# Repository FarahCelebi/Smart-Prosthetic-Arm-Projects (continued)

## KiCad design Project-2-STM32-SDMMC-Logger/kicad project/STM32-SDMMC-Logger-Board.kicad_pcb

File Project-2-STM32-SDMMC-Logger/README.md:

# STM32-SDMMC-Logger

An STM32F411-based data logger board with a 4-bit SDMMC interface to a
microSD card slot, designed as a companion to the EMG Acquisition Board.
The board receives dual-channel EMG data over I²C and logs it to a microSD
card in real time via FatFS, providing a self-contained data capture platform
for training the gesture classification firmware in the Smart Prosthetic Arm
system.

## Schematic

## PCB Layout

## 3D View

## Overview

The board pairs an STM32F411RETx (LQFP-64) with a push-push microSD card
slot over the SDMMC peripheral's 4-bit wide bus, capable of sustained write
speeds suitable for real-time dual-channel EMG logging at 1kHz sample rate.
A 25MHz crystal provides the accurate clock reference required for USB CDC
operation. Power comes from a micro-USB connector through a polyfuse and
AMS1117-3.3 LDO. A 4-pin I²C header matches the pinout of the EMG
Acquisition Board's J3 connector for direct cable connection.

## Design Notes

**MCU package selection:** The STM32F411 is available in UFQFPN-48 and
LQFP-64 packages. The UFQFPN-48 was initially considered but rejected because
the SDMMC peripheral requires PC8–PC12 and PD2, which are not bonded out on
the 48-pin package. The LQFP-64 exposes the full port C and port D, making
it the only viable option for 4-bit SDMMC operation on this device.

**SDMMC bus:** CLK, CMD, and DAT0–DAT3 connect the STM32's SDMMC peripheral
to the card slot using the standard STM32F4 pin mapping (PC12, PD2,
PC8–PC11). Each signal passes through a 47Ω series resistor placed close to
the STM32 to damp reflections at the card connector end. CMD and DAT0–DAT3
each have a 10kΩ pull-up to +3.3V — required by the SD specification to hold
these lines high during card initialisation before the card begins responding.
CLK has no pull-up since it is a push-pull output driven continuously by the
peripheral and is never in a high-impedance state.

**SDMMC signal integrity:** All six SDMMC signals are routed at 0.25mm width
on F.Cu with lengths kept as short as possible given the placement. The series
resistors are placed inline on each trace close to U2's pins. At the initial
operating frequency of 25MHz (half-speed mode, as used by FatFS during card
initialisation and typical logging workloads), the timing budget is generous
and the short trace lengths keep skew well within tolerance.

**Card detect:** The microSD connector includes a mechanical DET switch that
closes to GND when a card is inserted. This connects to PB7 with a 10kΩ
pull-up to +3.3V, keeping the GPIO high when no card is present and pulling
it low on insertion. The DAT3/CD pin on the card is used exclusively as DAT3
during normal 4-bit operation — the mechanical DET switch is used for card
presence detection to avoid conflicts with the data bus.

**Crystal and USB:** A 25MHz crystal (KC2520Z, 4-pad SMD) provides the
external clock reference for the STM32's PLL and USB peripheral. Load
capacitors C13 and C14 (12pF each) are placed immediately beside the PH0
and PH1 pins on U2, with no vias on the oscillator traces. The calculated
load capacitance is approximately 9pF, consistent with the crystal's
specification. USB D+ and D− are routed as a matched pair through the
USBLC6-2SC6 ESD protection device placed close to J1, then through 22Ω
series resistors before reaching PA11 and PA12.

**Power supply:** VBUS from J1 passes through a 500mA polyfuse (F1) before
reaching the AMS1117-3.3 LDO (U1). The polyfuse protects the USB host from
overcurrent faults and resets automatically once the fault clears. The LDO
input is decoupled with 10µF and 100nF capacitors; the output is decoupled
with 10µF and 100nF capacitors. All downstream logic and analog circuitry
runs from the 3.3V output.

**Stackup rationale:** This board uses a 2-layer stackup with signals and
power on F.Cu and a solid unbroken GND plane on B.Cu only — no GND pour on
F.Cu. For a digital board this configuration gives every F.Cu signal trace a
direct return path immediately beneath it, which is the optimal arrangement
for signal integrity. Adding a GND pour on F.Cu would fragment it with signal
traces, creating isolated copper islands that require stitching vias and
producing inconsistent return paths under SDMMC and USB signals. The solid
B.Cu plane handles all return currents cleanly without these compromises.
Stitching vias are placed around the board perimeter to tie the board edge
GND connections to the B.Cu plane.

**Decoupling:** The STM32F411RETx has four VDD pins and one VDDA pin, each
decoupled individually with a 100nF ceramic capacitor placed as close as
physically possible to the respective pin. The single VCAP1 pin is decoupled
with a 1µF capacitor as required by the internal core voltage regulator.
VBAT is decoupled with 100nF to GND.

## Manufacturing

- 2-layer stackup: F.Cu (signal + power) / B.Cu (solid GND plane)
- 1.6mm FR4, standard 1oz copper
- Passed DRC with 0 violations, 0 unconnected nets
- Gerbers and drill files generated

## Part of

Smart Prosthetic Arm — STM32-SDMMC-Logger #2

## Tools

- KiCad

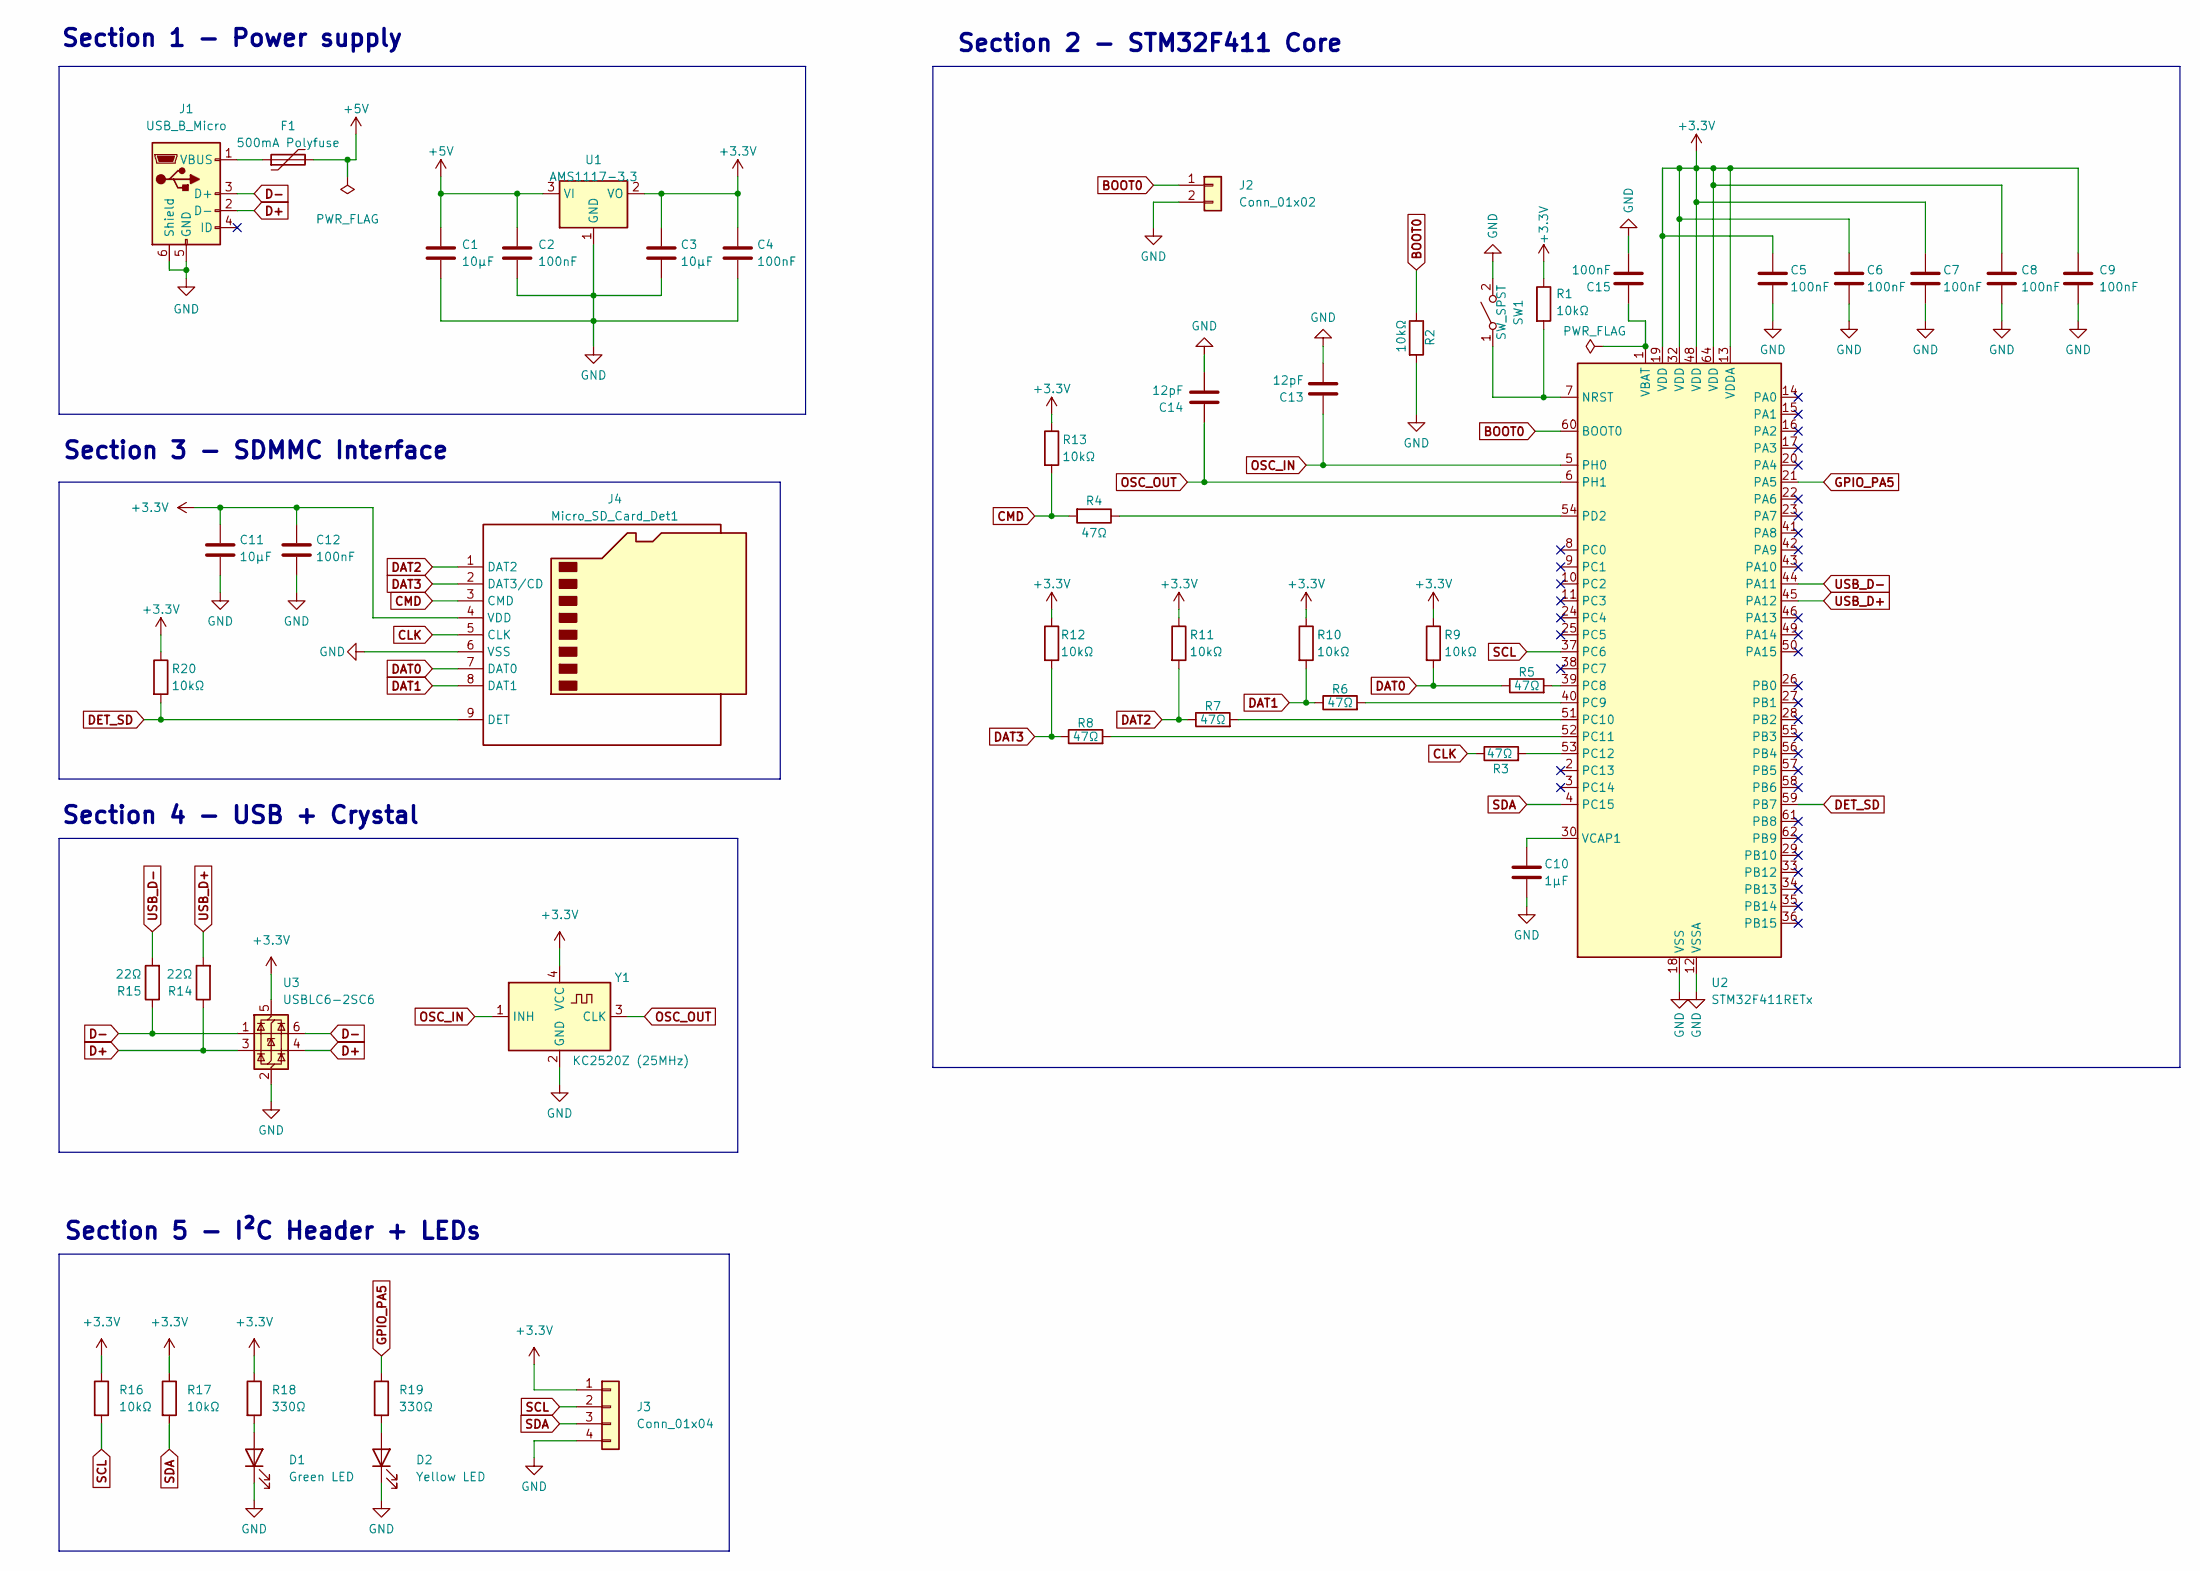
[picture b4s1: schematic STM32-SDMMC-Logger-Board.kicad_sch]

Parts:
C1, C3, C11: 10µF; C_0805_2012Metric
C2, C4, C5, C6, C7, C8, C9, C12, C15: 100nF; C_0402_1005Metric
C10: 1µF; C_0402_1005Metric
C13, C14: 12pF; C_0402_1005Metric
D1: Green LED; LED_0402_1005Metric
D2: Yellow LED; LED_0402_1005Metric
F1: 500mA Polyfuse; Fuse_1812_4532Metric
J1: USB_B_Micro; USB_Micro-B_Amphenol_10118194_Horizontal
J2: Conn_01x02; PinHeader_1x02_P2.54mm_Vertical
J3: Conn_01x04; FanPinHeader_1x04_P2.54mm_Vertical
J4: Micro_SD_Card_Det1; microSD_HC_Molex_47219-2001
R1, R2, R9, R10, R11, R12, R13, R16, R17, R20: 10kΩ; R_0402_1005Metric
R3, R4, R5, R6, R7, R8: 47Ω; R_0402_1005Metric
R14, R15: 22Ω; R_0402_1005Metric
R18, R19: 330Ω; R_0402_1005Metric
SW1: SW_SPST; SW_SPST_PTS645Sx43SMTR92
U1: AMS1117-3.3; SOT-223-3_TabPin2
U2: STM32F411RETx; LQFP-64_10x10mm_P0.5mm
U3: USBLC6-2SC6; SOT-23-6
Y1: KC2520Z (25MHz); Crystal_SMD_2520-4Pin_2.5x2.0mm

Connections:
+3.3V: C3.1, C4.1, C5.1, C6.1, C7.1, C8.1, C9.1, C11.1, C12.1, J3.1, J4.4 (VDD), R1.1, R9.1, R10.1, R11.1, R12.1, R13.1, R16.1, R17.1, R18.1, R20.1, U1.2 (VO), U2.13 (VDDA), U2.19 (VDD), U2.32 (VDD), U2.48 (VDD), U2.64 (VDD), U3.5 (VBUS), Y1.4 (VCC)
+5V: C1.1, C2.1, F1.2, U1.3 (VI)
BOOT0: J2.1, R2.1, U2.60 (BOOT0)
CLK: J4.5 (CLK), R3.1
CMD: J4.3 (CMD), R4.2, R13.2
D+: J1.2 (D-), R14.1, U3.3 (I/O2), U3.4 (I/O2)
D-: J1.3 (D+), R15.1, U3.1 (I/O1), U3.6 (I/O1)
DAT0: J4.7 (DAT0), R5.1, R9.2
DAT1: J4.8 (DAT1), R6.1, R10.2
DAT2: J4.1 (DAT2), R7.1, R11.2
DAT3: J4.2 (DAT3/CD), R8.1, R12.2
DET_SD: J4.9 (DET), R20.2, U2.59 (PB7)
GND: C1.2, C2.2, C3.2, C4.2, C5.2, C6.2, C7.2, C8.2, C9.2, C10.2, C11.2, C12.2, C13.2, C14.2, C15.2, D1.1 (K), D2.1 (K), J1.5 (GND), J1.6 (Shield), J2.2, J3.4, J4.6 (VSS), R2.2, SW1.2 (B), U1.1 (GND), U2.12 (VSSA), U2.18 (VSS), U2.31 (VSS), U2.47 (VSS), U2.63 (VSS), U3.2 (GND), Y1.2 (GND)
GPIO_PA5: R19.1, U2.21 (PA5)
unnamed: D1.2 (A), R18.2
unnamed: D2.2 (A), R19.2
unnamed: F1.1, J1.1 (VBUS)
unnamed: R1.2, SW1.1 (A), U2.7 (NRST)
unnamed: R5.2, U2.39 (PC8)
unnamed: R6.2, U2.40 (PC9)
unnamed: R7.2, U2.51 (PC10)
unnamed: R8.2, U2.52 (PC11)
unnamed: R3.2, U2.53 (PC12)
unnamed: R4.1, U2.54 (PD2)
unnamed: C15.1, U2.1 (VBAT)
unnamed: C10.1, U2.30 (VCAP1)
OSC_IN: C13.1, U2.5 (PH0), Y1.1 (INH)
OSC_OUT: C14.1, U2.6 (PH1), Y1.3 (CLK)
SCL: J3.2, R16.2, U2.37 (PC6)
SDA: J3.3, R17.2, U2.4 (PC15)
USB_D+: R14.2, U2.45 (PA12)
USB_D-: R15.2, U2.44 (PA11)

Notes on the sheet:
Section 3 - SDMMC Interface
Section 2 - STM32F411 Core
Section 4 - USB + Crystal
Section 1 - Power supply
Section 5 - I²C Header + LEDs

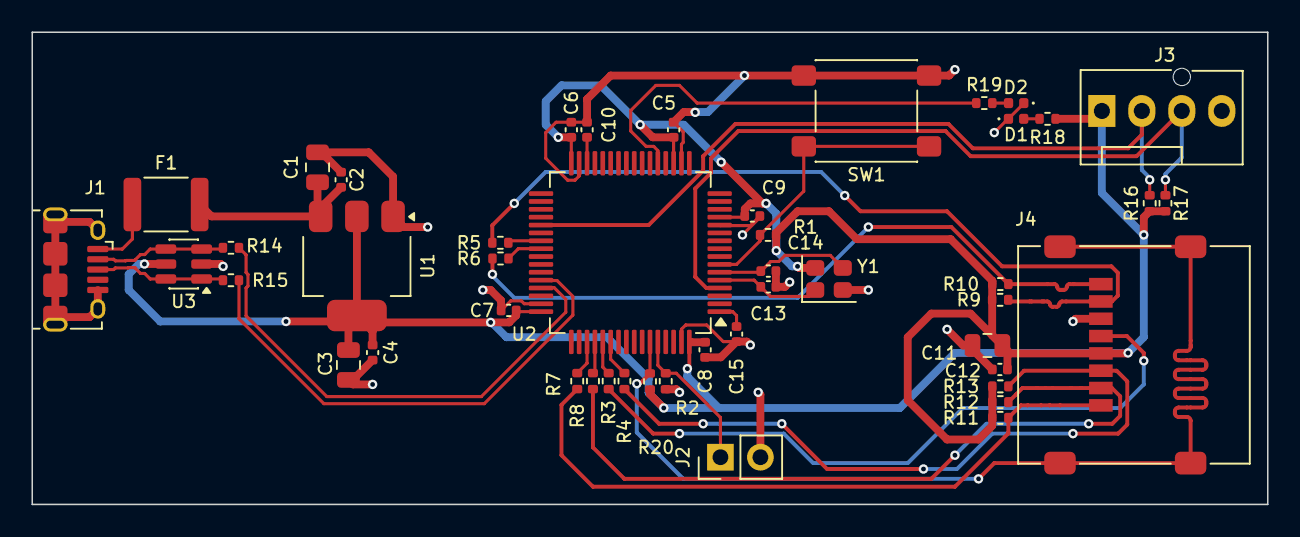
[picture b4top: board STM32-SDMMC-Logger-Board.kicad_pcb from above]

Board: 2 copper layers, 78.5 x 30.0 mm, 47 parts (0 on the bottom side), 32 nets.

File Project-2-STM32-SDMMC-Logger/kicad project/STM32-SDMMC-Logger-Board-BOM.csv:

"Id";"Designator";"Footprint";"Quantity";"Designation";"Supplier and ref";
1;"C14,C13";"C_0402_1005Metric";2;"12pF";;;
2;"Y1";"Crystal_SMD_2520-4Pin_2.5x2.0mm";1;"KC2520Z (25MHz)";;;
3;"R14,R15";"R_0402_1005Metric";2;"22Ω";;;
4;"U3";"SOT-23-6";1;"USBLC6-2SC6";;;
5;"F1";"Fuse_1812_4532Metric";1;"500mA Polyfuse";;;
6;"R10,R9,R1,R20,R12,R16,R17,R11,R2,R13";"R_0402_1005Metric";10;"10kΩ";;;
7;"C1,C11,C3";"C_0805_2012Metric";3;"10µF";;;
8;"C10";"C_0402_1005Metric";1;"1µF";;;
9;"J2";"PinHeader_1x02_P2.54mm_Vertical";1;"Conn_01x02";;;
10;"R19,R18";"R_0402_1005Metric";2;"330Ω";;;
11;"C8,C2,C7,C12,C6,C4,C9,C15,C5";"C_0402_1005Metric";9;"100nF";;;
12;"D1";"LED_0402_1005Metric";1;"Green LED";;;
13;"SW1";"SW_SPST_PTS645Sx43SMTR92";1;"SW_SPST";;;
14;"U1";"SOT-223-3_TabPin2";1;"AMS1117-3.3";;;
15;"J3";"FanPinHeader_1x04_P2.54mm_Vertical";1;"Conn_01x04";;;
16;"R3,R6,R4,R5,R8,R7";"R_0402_1005Metric";6;"47Ω";;;
17;"J1";"USB_Micro-B_Amphenol_10118194_Horizontal";1;"USB_B_Micro";;;
18;"D2";"LED_0402_1005Metric";1;"Yellow LED";;;
19;"U2";"LQFP-64_10x10mm_P0.5mm";1;"STM32F411RETx";;;
20;"J4";"microSD_HC_Molex_47219-2001";1;"Micro_SD_Card_Det1";;;

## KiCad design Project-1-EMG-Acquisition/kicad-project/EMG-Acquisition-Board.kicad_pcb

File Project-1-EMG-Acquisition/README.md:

# EMG-Acquisition-Board

A dual-channel electromyography (EMG) signal acquisition board for surface
electrode input, designed as Project 1 of the Smart Prosthetic Arm system.
The board conditions raw muscle electrical signals into a clean, amplified,
digitised output suitable for real-time gesture classification firmware.

## Schematic

## PCB Layout

## 3D View

## Overview

Surface EMG signals are weak (50µV–5mV), heavily contaminated by DC electrode
offset, motion artefact, and 50Hz mains interference. This board addresses
each of these with a structured four-stage signal chain: differential
instrumentation amplification, AC coupling, a second gain stage, and
anti-alias filtering before a 16-bit I²C ADC. Total gain per channel is
approximately 404×, placing a 1mV EMG input at roughly 400mV at the ADC input
— well within the ADS1115's input range referenced to a 1.65V mid-rail.

## Design Notes

**Mid-rail bias generation:** The entire analog chain operates from a single
3.3V supply, which requires a stable 1.65V mid-rail reference to centre
signals within the supply range. A resistor divider (R1, R2 — 100kΩ each)
sets the VMID node at 1.65V, filtered by a 10µF capacitor (C3) to suppress
supply noise. A TLV6001DCK op-amp wired as a unity-gain voltage follower
buffers this reference (VMID_BUF), providing a low-impedance 1.65V rail that
drives the INA333 REF pins and the second-stage amplifier bias inputs. Without
the buffer, loading from the REF pins would pull VMID off its setpoint under
signal conditions.

**First-stage instrumentation amplifier:** Each channel uses an INA333 (SOIC-8)
configured for approximately 101× differential gain, set by a single 1kΩ gain
resistor (Rg) via the formula G = 1 + 100kΩ/Rg. The INA333 was selected for
its low offset voltage (25µV typical), low input bias current suitable for
high-impedance electrode sources, and single-supply rail-to-rail operation
down to 1.8V. The REF pin is tied to VMID_BUF on both channels, centering
the amplifier output at 1.65V. Input bias resistors (R3, R4 and R6, R7 —
1MΩ each) hold each differential input at VMID_BUF when no electrode is
connected, preventing the instrumentation amplifier inputs from floating and
the output from railing.

**AC coupling and high-pass filter:** The INA333 output passes through an RC
high-pass filter (C5/C7 — 10µF, R5/R8 — 10kΩ) with a cutoff frequency of
approximately 1.6Hz, calculated as f = 1/(2π × 10kΩ × 10µF). This removes
the residual DC electrode offset that survives the differential stage —
typically several hundred millivolts in practical electrode setups — while
passing all physiologically relevant EMG content above 20Hz with minimal
attenuation.

**Second-stage amplifier:** A TLV2372 dual op-amp (SOIC-8) provides 4×
additional gain per channel in a non-inverting topology, with the output
biased at VMID_BUF through the lower feedback resistor. Gain is set by the
ratio 1 + R13/R11 = 1 + 30kΩ/10kΩ = 4×. This stage also drives the
anti-alias filter, which a high-output-impedance source such as the RC filter
output could not do reliably.

**Anti-alias filter:** A first-order RC low-pass filter (R15/R16 — 3.3kΩ,
C9/C10 — 100nF) on each channel output sets the anti-alias cutoff at
approximately 480Hz, calculated as f = 1/(2π × 3.3kΩ × 100nF). This sits
just below the Nyquist frequency for a 1kHz ADC sampling rate, suppressing
out-of-band noise and aliasing artefacts before the signal reaches the ADC
input.

**ADC and I²C interface:** The ADS1115IDGS (MSOP-10) is a 16-bit successive-
approximation ADC with an internal programmable gain amplifier and I²C
interface. Channels AIN0 and AIN1 receive CH1_ADC and CH2_ADC respectively;
AIN2 and AIN3 are tied to GND. The ADDR pin is tied to GND, setting the I²C
address to 0x48. VDD is decoupled with a 100nF ceramic capacitor and a 10µF
bulk capacitor. I²C pull-up resistors (R17, R18 — 10kΩ each to +3.3V) are
placed immediately adjacent to J3, the 4-pin I²C header (VCC, GND, SCL, SDA),
which connects to the host microcontroller.

**Signal chain summary:**

| Stage | Component | Gain / Function |
|---|---|---|
| Instrumentation amp | INA333 × 2 | 101× differential |
| High-pass filter | RC (10µF, 10kΩ) | −3dB at 1.6Hz |
| Second stage | TLV2372 × 2 | 4× non-inverting |
| Anti-alias filter | RC (100nF, 3.3kΩ) | −3dB at 480Hz |
| ADC | ADS1115 | 16-bit, I²C, 0x48 |
| **Total gain** | | **~404×** |

## Manufacturing

- 2-layer stackup: F.Cu (signal + power) / B.Cu (GND plane)
- 1.6mm FR4, standard 1oz copper
- Passed DRC with 0 violations, 0 unconnected nets
- Gerbers and drill files generated

## Part of

Smart Prosthetic Arm — Project 1 of 6

## Tools

- KiCad

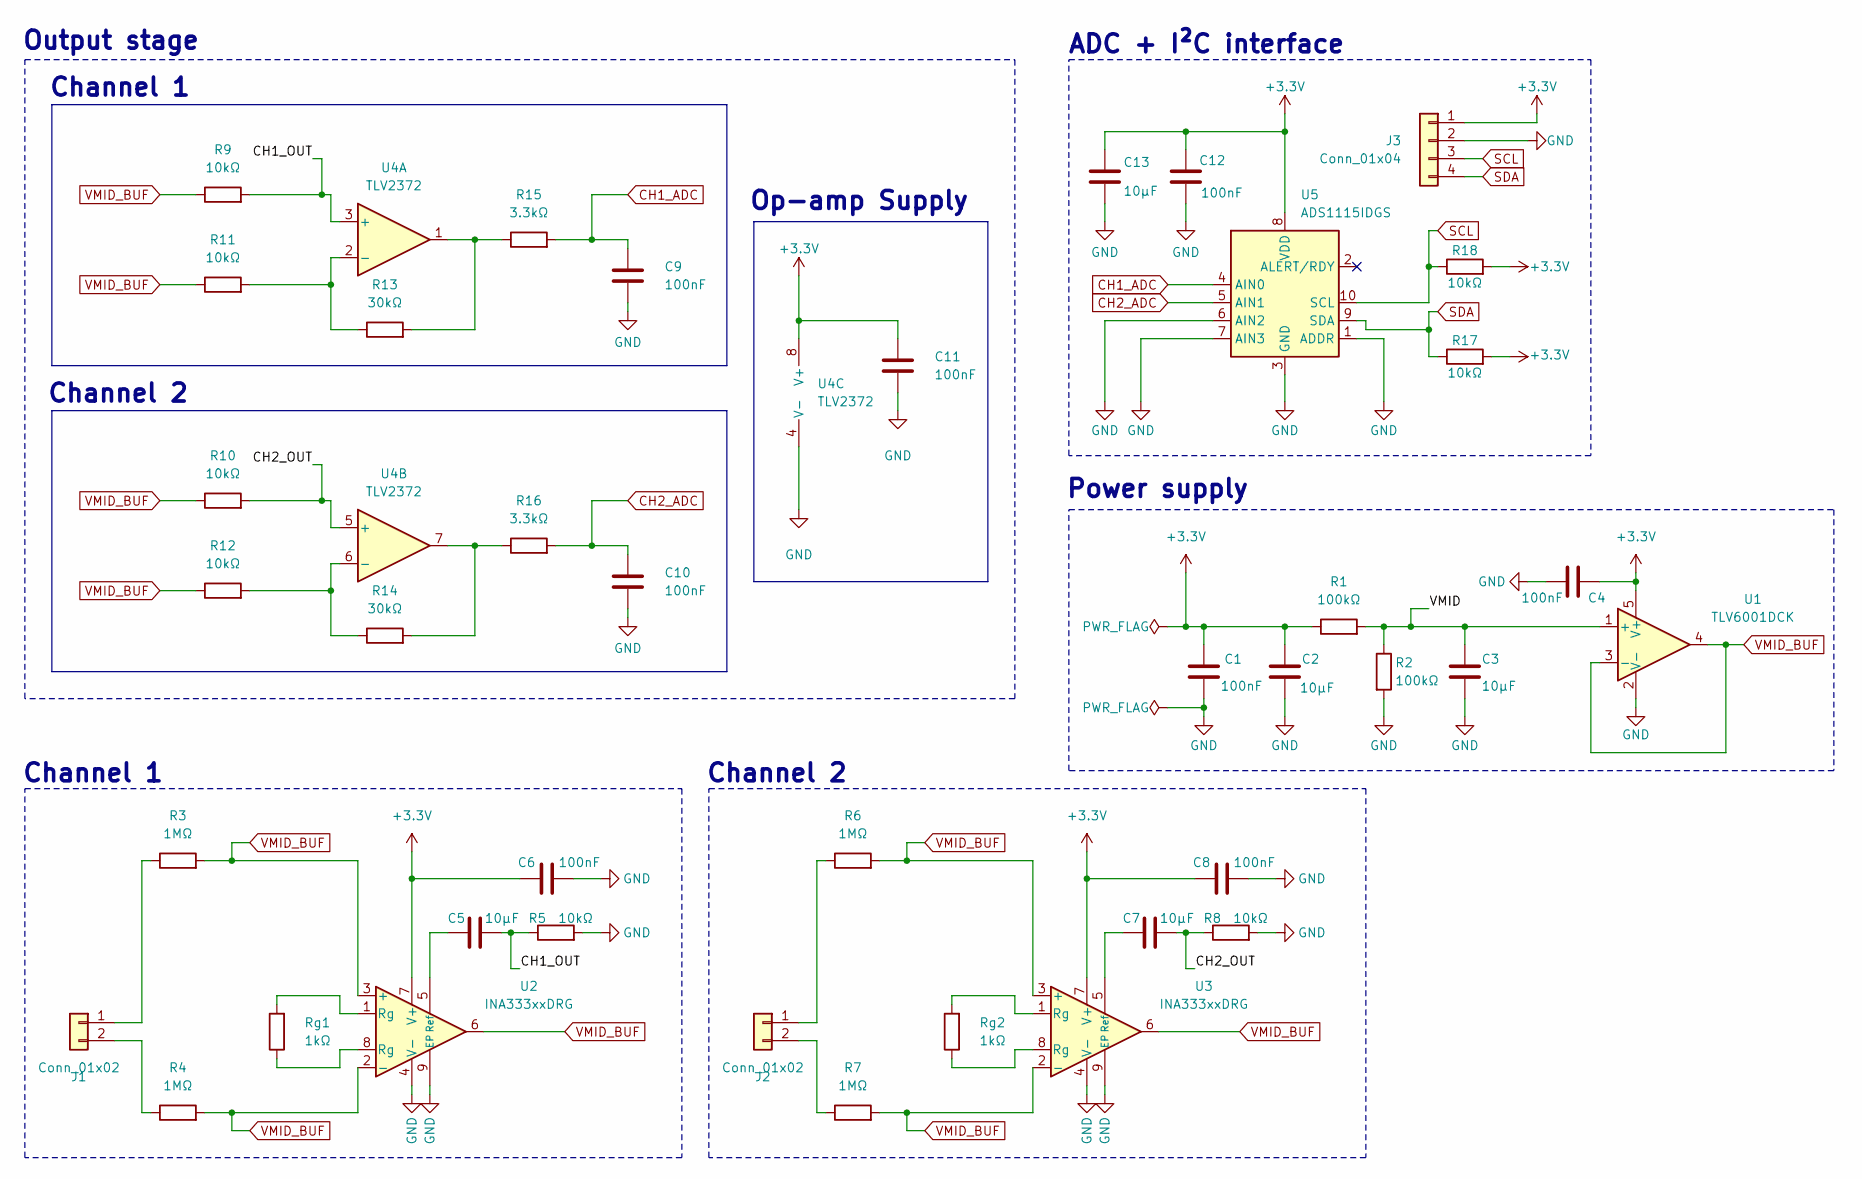
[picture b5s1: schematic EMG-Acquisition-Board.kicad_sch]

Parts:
C1, C4, C6, C8, C9, C10, C11, C12: 100nF; C_0402_1005Metric
C2, C3, C5, C7, C13: 10µF; C_0805_2012Metric
J1, J2: Conn_01x02; PinHeader_1x02_P2.54mm_Vertical
J3: Conn_01x04; PinHeader_1x04_P2.54mm_Vertical
R1, R2: 100kΩ; R_0402_1005Metric
R3, R4, R6, R7: 1MΩ; R_0402_1005Metric
R5, R8, R9, R10, R11, R12, R17, R18: 10kΩ; R_0402_1005Metric
R13, R14: 30kΩ; R_0402_1005Metric
R15, R16: 3.3kΩ; R_0402_1005Metric
Rg1, Rg2: 1kΩ; R_0402_1005Metric
U1: TLV6001DCK; SOT-353_SC-70-5
U2, U3: INA333xxDRG; WSON-8-1EP_3x3mm_P0.5mm_EP1.45x2.4mm
U4: TLV2372; SOIC-8_3.9x4.9mm_P1.27mm
U5: ADS1115IDGS; TSSOP-10_3x3mm_P0.5mm

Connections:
+3.3V: C1.1, C2.1, C4.1, C6.1, C8.1, C11.1, C12.1, C13.1, J3.1, R1.1, R17.2, R18.2, U1.5 (V+), U2.7 (V+), U3.7 (V+), U4.8 (V+), U5.8 (VDD)
/CH1_OUT: C5.2, R5.1, R9.2, U4.3 (+)
/CH2_OUT: C7.2, R8.1, R10.2, U4.5 (+)
/VMID: C3.1, R1.2, R2.1, U1.1 (+)
CH1_ADC: C9.1, R15.2, U5.4 (AIN0)
CH2_ADC: C10.1, R16.2, U5.5 (AIN1)
GND: C1.2, C2.2, C3.2, C4.2, C6.2, C8.2, C9.2, C10.2, C11.2, C12.2, C13.2, J3.2, R2.2, R5.2, R8.2, U1.2 (V-), U2.4 (V-), U2.9 (EP), U3.4 (V-), U3.9 (EP), U4.4 (V-), U5.1 (ADDR), U5.3 (GND), U5.6 (AIN2), U5.7 (AIN3)
unnamed: J1.1, R3.1
unnamed: J1.2, R4.1
unnamed: J2.1, R6.1
unnamed: J2.2, R7.1
unnamed: R13.2, R15.1, U4.1
unnamed: R14.2, R16.1, U4.7
unnamed: Rg1.1, U2.8 (Rg)
unnamed: Rg1.2, U2.1 (Rg)
unnamed: Rg2.1, U3.8 (Rg)
unnamed: Rg2.2, U3.1 (Rg)
unnamed: C5.1, U2.5 (Ref)
unnamed: C7.1, U3.5 (Ref)
unnamed: R11.2, R13.1, U4.2 (-)
unnamed: R12.2, R14.1, U4.6 (-)
SCL: J3.3, R18.1, U5.10 (SCL)
SDA: J3.4, R17.1, U5.9 (SDA)
VMID_BUF: R3.2, R4.2, R6.2, R7.2, R9.1, R10.1, R11.1, R12.1, U1.3 (-), U1.4, U2.2 (-), U2.3 (+), U2.6, U3.2 (-), U3.3 (+), U3.6

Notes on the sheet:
Power supply
ADC + I²C interface
Op-amp Supply
Output stage
Channel 2
Channel 1

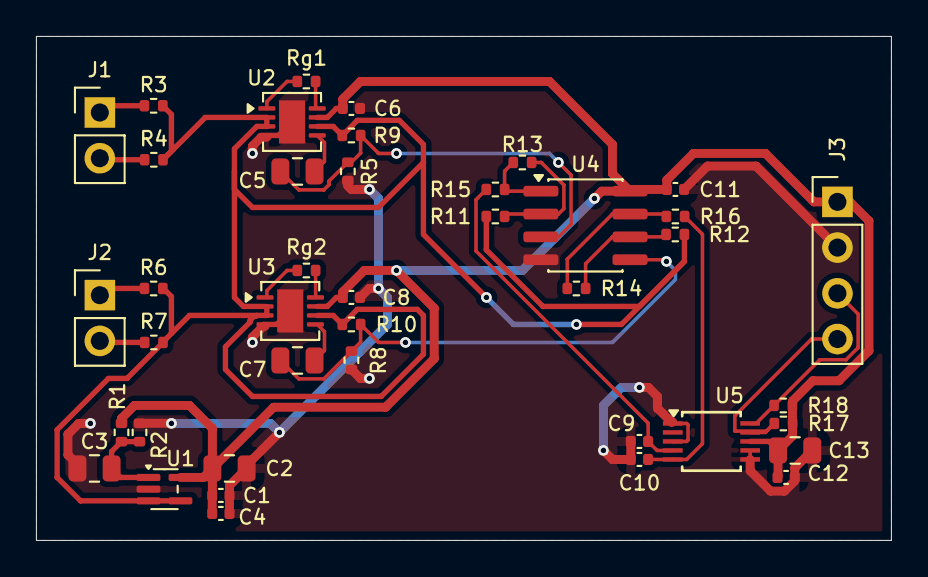
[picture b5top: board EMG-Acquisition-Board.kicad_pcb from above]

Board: 2 copper layers, 47.5 x 28.0 mm, 41 parts (0 on the bottom side), 24 nets.

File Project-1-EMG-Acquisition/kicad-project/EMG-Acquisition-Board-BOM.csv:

"Id";"Designator";"Footprint";"Quantity";"Designation";"Supplier and ref";
1;"R5,R12,R9,R18,R11,R17,R10,R8";"R_0402_1005Metric";8;"10kΩ";;;
2;"C11,C4,C1,C6,C10,C12,C8,C9";"C_0402_1005Metric";8;"100nF";;;
3;"R1,R2";"R_0402_1005Metric";2;"100kΩ";;;
4;"U4";"SOIC-8_3.9x4.9mm_P1.27mm";1;"TLV2372";;;
5;"R16,R15";"R_0402_1005Metric";2;"3.3kΩ";;;
6;"R4,R7,R3,R6";"R_0402_1005Metric";4;"1MΩ";;;
7;"Rg1,Rg2";"R_0402_1005Metric";2;"1kΩ";;;
8;"C2,C7,C3,C5,C13";"C_0805_2012Metric";5;"10µF";;;
9;"R13,R14";"R_0402_1005Metric";2;"30kΩ";;;
10;"U5";"TSSOP-10_3x3mm_P0.5mm";1;"ADS1115IDGS";;;
11;"U2,U3";"WSON-8-1EP_3x3mm_P0.5mm_EP1.45x2.4mm";2;"INA333xxDRG";;;
12;"J1,J2";"PinHeader_1x02_P2.54mm_Vertical";2;"Conn_01x02";;;
13;"U1";"SOT-353_SC-70-5";1;"TLV6001DCK";;;
14;"J3";"PinHeader_1x04_P2.54mm_Vertical";1;"Conn_01x04";;;

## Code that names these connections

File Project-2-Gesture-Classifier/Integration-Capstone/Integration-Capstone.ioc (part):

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Mcu.Name=STM32F411R(C-E)Tx
Mcu.Package=LQFP64
Mcu.UserName=STM32F411RCTx
PA10.Mode=Asynchronous
PA10.Signal=USART1_RX
PA11.Mode=Device_Only
PA11.Signal=USB_OTG_FS_DM
PA12.Mode=Device_Only
PA12.Signal=USB_OTG_FS_DP
PA3.GPIOParameters=GPIO_Speed,PinState,GPIO_Label
PA3.GPIO_Label=LED_BLE
PA3.GPIO_Speed=GPIO_SPEED_FREQ_MEDIUM
PA3.PinState=GPIO_PIN_SET
PA3.Signal=GPIO_Output
PA4.GPIOParameters=GPIO_Speed,PinState,GPIO_Label
PA4.GPIO_Label=IMU_CS
PA4.GPIO_Speed=GPIO_SPEED_FREQ_MEDIUM
PA4.PinState=GPIO_PIN_SET
PA4.Signal=GPIO_Output
PA5.Mode=Full_Duplex_Master
PA5.Signal=SPI1_SCK
PA6.Mode=Full_Duplex_Master
PA6.Signal=SPI1_MISO
PA7.Mode=Full_Duplex_Master
PA7.Signal=SPI1_MOSI
PA9.Mode=Asynchronous
PA9.Signal=USART1_TX
PB0.GPIOParameters=GPIO_Speed,PinState,GPIO_Label
PB0.GPIO_Label=LED_GESTURE
PB0.GPIO_Speed=GPIO_SPEED_FREQ_MEDIUM
PB0.PinState=GPIO_PIN_SET
PB0.Signal=GPIO_Output
PB10.Mode=I2C
PB10.Signal=I2C2_SCL
PB6.Mode=I2C
PB6.Signal=I2C1_SCL
PB7.Mode=I2C
PB7.Signal=I2C1_SDA
PB9.Mode=I2C
PB9.Signal=I2C2_SDA
PH0\ -\ OSC_IN.Mode=HSE-External-Oscillator
PH0\ -\ OSC_IN.Signal=RCC_OSC_IN
PH1\ -\ OSC_OUT.Mode=HSE-External-Oscillator
PH1\ -\ OSC_OUT.Signal=RCC_OSC_OUT
RCC.HSE_VALUE=25000000
RCC.SYSCLKFreq_VALUE=48000000
RCC.SYSCLKSource=RCC_SYSCLKSOURCE_PLLCLK
board=custom
